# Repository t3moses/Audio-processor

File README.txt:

Hardware

The ADCs and DACs use the SPI protocol.  ADCs and DACs run on independent time-bases.  While, initially, they will be synchronized, future applications may require them to run independently.

ADC - The analog-to-digital converters are Texas Instruments ADS7042 12-bit single-channel ADCs with SPI interface.

DAC - The digital-to-analog converter is a Microchip MCP4822 12-bit 2-channel DAC with SPI interface.

The XLR input and output are single-channel, while the TRS input and output are 2-channel.  XLR and TRS do not operate simultaneously.  So, the XLR channel and the TRS tip (or left channel) are combined.

Processor

Computation is performed by a Xiao SEEED dev-board with an Espressif ESP32C3 processor.

Software

The only function required initially is direct analog-in to analog-out through the processor.

Timers

It uses the esp_timer library.  The file sdkconfig.h is included in order that timers can call interrupt handlers directly.

Left and right ADCs are separate SPI devices, whereas the dual DAC is one SPI device.

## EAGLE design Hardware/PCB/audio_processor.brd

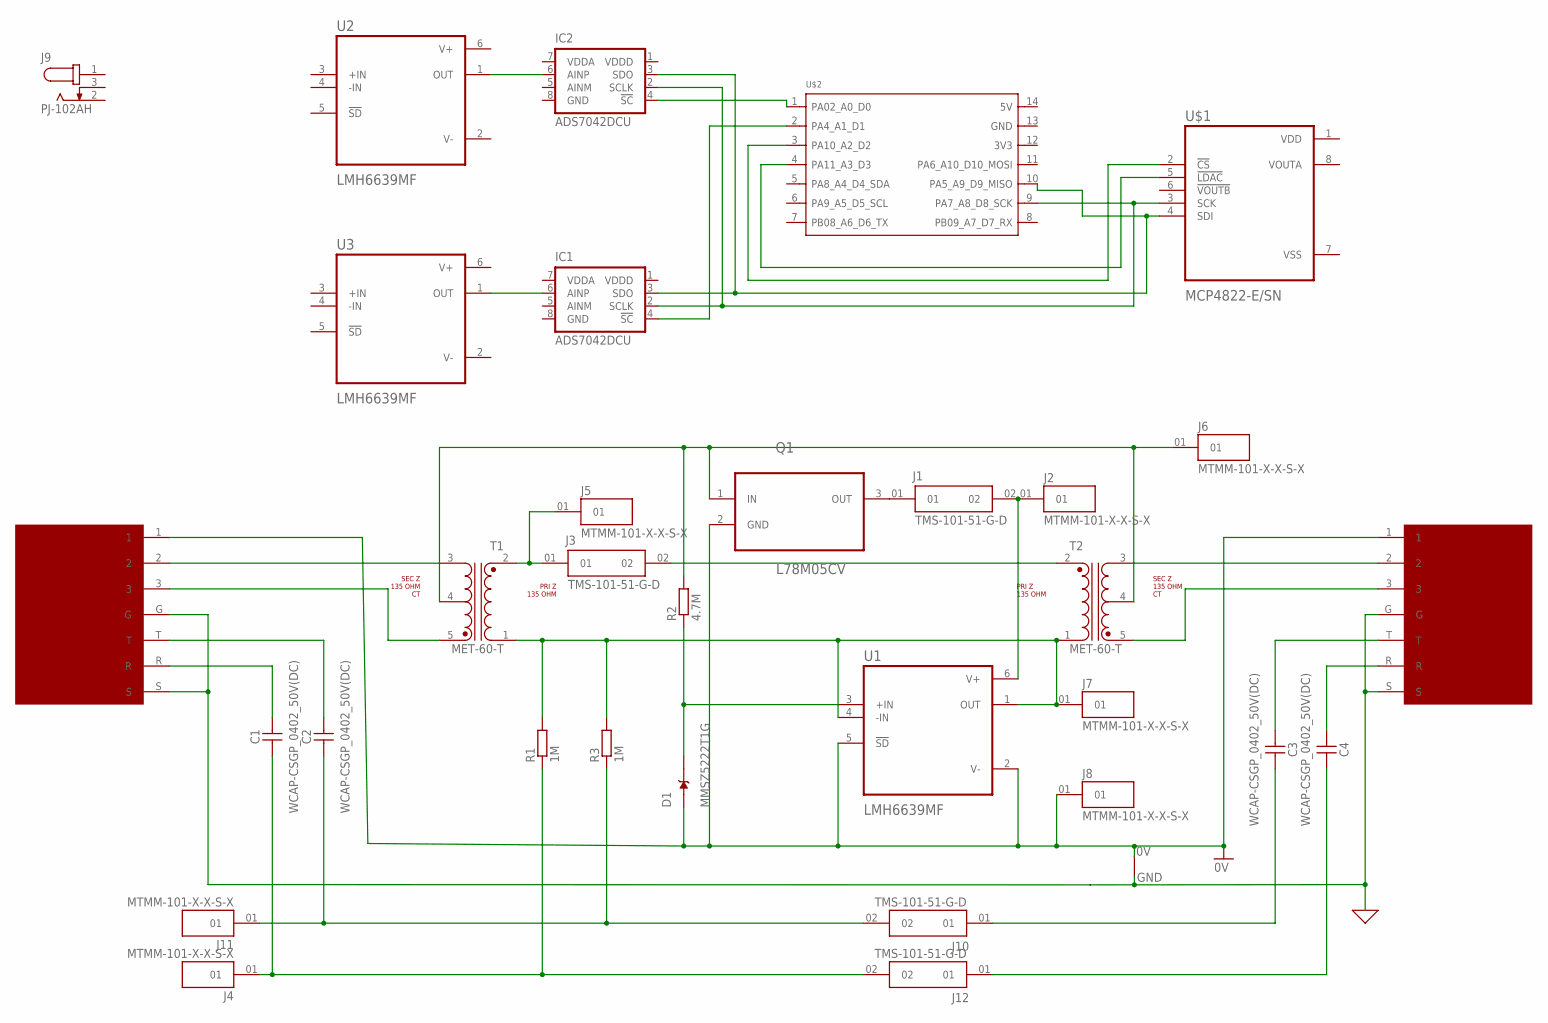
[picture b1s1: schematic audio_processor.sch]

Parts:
B1: NET_BRIDGE
C1, C2, C3, C4: WCAP-CSGP_0402_50V(DC); WCAP-CSGP_0402; LCSC C1581
C5, C6: XLR-TRS-THRU-HOLE-FEMALE-AMPHENOL
D1: MMSZ5222T1G; SOD3716X135N; LCSC C150078
IC1, IC2: ADS7042DCU; DCU_(R-PDSO-G8)
J1, J3, J10, J12: TMS-101-51-G-D; SAMTEC_TMS-101-51-G-D
J2, J4, J5, J6, J7, J8, J11: MTMM-101-X-X-S-X; SAMTEC_MTMM-101-X-X-S-X
J9: PJ-102AH; CUI_PJ-102AH
Q1: L78M05CV; TO254P450X1020X1935-3P; LCSC C283462
R1, R3: 1M; R0402; LCSC C26083
R2: 4.7M; R0402; LCSC C26091
T1, T2: MET-60-T; XFMR_MET-60-T
U1, U2, U3: LMH6639MF; SOT95P280X145-6N; LCSC C131982
U$1: MCP4822-E/SN; SOIC127P599X175-8N
U$2: SEEED_ESP32_C3; MOUDLE14P-2.54-21X17.8MM

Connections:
0V: B1.P$1 (1), C5.1, C6.1, D1.2 (A), J8.01, Q1.2 (GND), U1.2 (V-), U1.5 (!SD)
GND: B1.P$2 (2), C5.G, C5.S, C6.G, C6.S, IC1.8 (GND), IC2.8 (GND)
unnamed: C6.2, T1.3
unnamed: C6.3, T1.5
unnamed: C5.2, T2.3
unnamed: C5.3, T2.5
unnamed: J6.01, Q1.1 (IN), R2.2, T1.4, T2.4
unnamed: D1.1 (C), R2.1, U1.3 (+IN)
unnamed: J7.01, R1.2, R3.2, T1.1, T2.1, U1.1 (OUT), U1.4 (-IN)
unnamed: C1.1, J4.01, J12.02, R1.1
unnamed: J3.01, J5.01, T1.2
unnamed: J3.02, T2.2
unnamed: C3.2, J10.01
unnamed: C4.1, C5.R
unnamed: C2.2, C6.T
unnamed: J1.01, Q1.3 (OUT)
unnamed: C1.2, C6.R
unnamed: C2.1, J10.02, J11.01, R3.1
unnamed: C3.1, C5.T
unnamed: C4.2, J12.01
unnamed: J1.02, J2.01, U1.6 (V+)
unnamed: U$1.5 (!LDAC), U$2.4 (PA11_A3_D3)
unnamed: IC1.2 (SCLK), IC2.2 (SCLK), U$1.3 (SCK), U$2.9 (PA7_A8_D8_SCK)
unnamed: IC2.6 (AINP), U2.1 (OUT)
unnamed: IC1.6 (AINP), U3.1 (OUT)
unnamed: IC1.3 (SDO), IC2.3 (SDO), U$1.4 (SDI), U$2.10 (PA5_A9_D9_MISO)
unnamed: IC1.4 (!SC), U$2.2 (PA4_A1_D1)
unnamed: IC2.4 (!SC), U$2.1 (PA02_A0_D0)
unnamed: U$1.2 (!CS), U$2.3 (PA10_A2_D2)
V+: U2.6 (V+), U3.6 (V+)
V-: U2.2 (V-), U3.2 (V-)
VDD: U$1.1 (VDD)
VDDA: IC1.7 (VDDA), IC2.7 (VDDA)
VDDD: IC1.1 (VDDD), IC2.1 (VDDD)
VSS: U$1.7 (VSS)

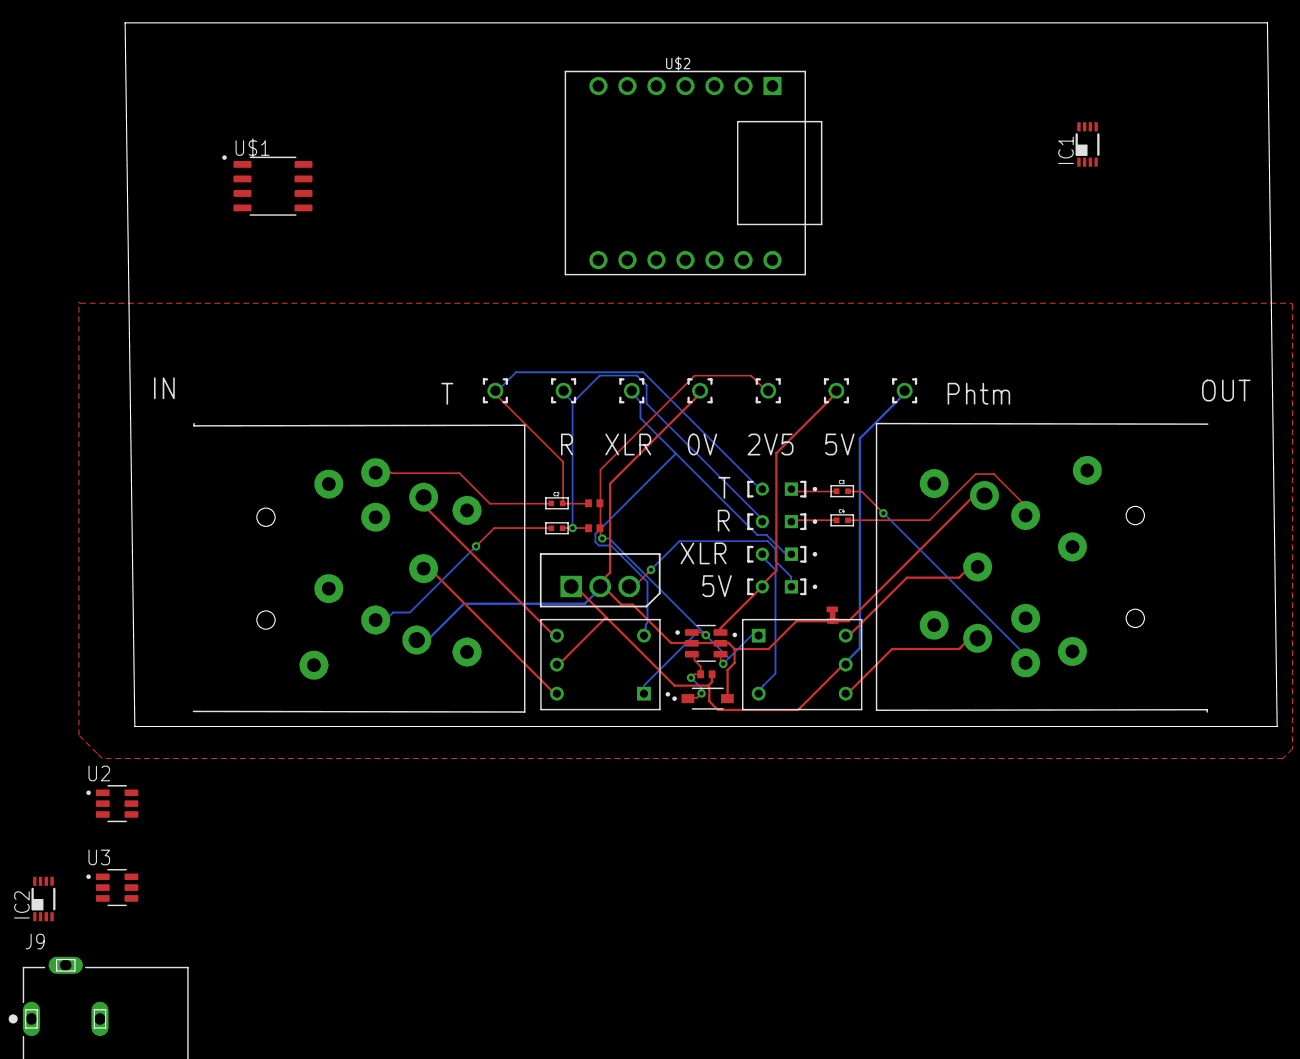
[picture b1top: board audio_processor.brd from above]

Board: 2 copper layers, 109.5 x 88.0 mm, 33 parts (0 on the bottom side), 33 nets.

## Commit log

2025-03-05 AP_0_00
    Files submitted to JCLPCB.
2025-03-11 AP_0_01
    Added C code from Midifier product.
2025-03-11 AP_0_02
    More README detail.
2025-03-17 AP_0_03
    First public commit. Uses timer group (as opposed to GPTimer).
2025-03-19 AP_0_04
    Replaces legacy timers with the esp_timer library.
2025-03-21 AP_0_05
    Updated README.
    Barrel connector library added.
